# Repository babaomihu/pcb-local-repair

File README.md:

# PCB Local Repair

**KiCad 局部布线修复工具 / Local PCB Routing Repair for KiCad**

[中文](#中文) · [English](#english) · [安装与操作 / Installation](docs/INSTALL.md)

## 中文

PCB Local Repair 用于修复 KiCad PCB 中选定的未连接项。选择需要修复的连接后，工具自动确定局部范围、尝试布线，并检查连接关系、设计规则和修改范围，生成可审查、可另存的修复结果。

提供 **KiCad 插件和命令行** 两种使用方式，支持单条连接修复与多条连接批量处理。布线任务在工程副本上运行，结果通过验收后，由用户决定另存或采纳。

### 主要功能

- **待修连接发现**：列出支持修复的未连接项，支持焊盘、已有走线与过孔端点。
- **自动确定范围**：根据选定连接生成局部修复区域，无需手动填写坐标。
- **多连接处理**：一次选择多条连接，按队列处理，并支持修复顺序调整和候选组合。
- **局部修复策略**：支持补线、受控推挤、拆线重布、有限跨层打孔及已有过孔复用。
- **精细修改权限**：指定允许移动的走线、允许重填的铺铜和可使用的层；支持只调整跨区走线的区域内部分。
- **原生检查与保护**：重新填铜后检查目标连接、原有连接和完整板级 DRC，核对规则与受保护区域。
- **结果审查与保存**：提供修改清单、前后对比、失败诊断和运行日志；合格结果可一键另存，也可备份后明确采纳到原工程。

### 使用流程

1. 按[安装文档](docs/INSTALL.md)准备环境并安装插件或 CLI。
2. 打开已保存的 PCB 工程，检查待修连接。
3. 选择一条或多条连接，设置允许的修改，启动修复。
4. 查看结果与修改清单，将通过验收的结果另存，或明确采纳。

命令行示例：

```sh
# 检查待修连接
pcb-local inspect --config runtime.json --board /path/to/board.kicad_pcb \
  --auto-region --layer F.Cu --out-dir tasks/inspect-001

# 将 TARGET_ID 替换为检查结果中的连接 ID
pcb-local repair --config runtime.json --board /path/to/board.kicad_pcb \
  --auto-region --layer F.Cu --inspection tasks/inspect-001/result.json \
  --target TARGET_ID --signal-kind ordinary-single-ended \
  --candidate-strategy auto --out-dir tasks/repair-001

# 另存通过验收的修复结果
pcb-local export-result tasks/repair-001 --destination outputs/repaired-001
```

当前版本 **0.9.5.dev13**，适用环境为 **macOS Apple Silicon、Python 3.12、KiCad 10.0.4**。面向普通单端信号的局部修复；具体参数、批量操作和插件安装见[使用文档](docs/INSTALL.md)。

## English

PCB Local Repair repairs selected unfinished connections in KiCad PCB projects. After you select a connection, it determines a local region, attempts routing, and checks connectivity, design rules, and modification permissions to produce a result you can review and save.

Use it through a **KiCad plugin or command-line interface**. It supports individual connections and selected batches. Routing runs on project copies; accepted results can be exported or explicitly adopted by the user.

### Features

- **Connection discovery:** list eligible unfinished connections involving pads, existing tracks, and vias.
- **Automatic local regions:** derive the repair area from the selected connection without manually entering coordinates.
- **Batch repair:** select multiple connections, process a queue, and use ordering and candidate-combination strategies.
- **Local routing strategies:** add tracks, perform controlled shove and rip-up/reroute, add a bounded number of through vias, and reuse existing vias.
- **Explicit permissions:** select movable tracks, refillable zones, and permitted layers; modify only the in-region portion of eligible tracks crossing the boundary.
- **Native validation:** refill zones, check target and existing connectivity, run full-board DRC, and verify rules and protected regions.
- **Review and delivery:** inspect change lists, before/after reports, failure diagnostics, and logs. Export accepted results or explicitly adopt them with a backup.

### Workflow

1. Follow the [installation guide](docs/INSTALL.md) to prepare the runtime and install the plugin or CLI.
2. Inspect a saved PCB project for eligible unfinished connections.
3. Select one or more connections, choose modification permissions, and start repair.
4. Review the changes, then export or explicitly adopt accepted results.

The CLI example above demonstrates inspection, repair, and export. Replace `TARGET_ID` with an ID returned by inspection.

Current version: **0.9.5.dev13**. Target environment: **macOS Apple Silicon, Python 3.12, KiCad 10.0.4**. The tool handles local repairs of ordinary single-ended signals. See the [usage guide](docs/INSTALL.md) for batch processing, permissions, and plugin setup.

## 目录 / Repository layout

```text
src/pcb_local/     CLI、修复策略与验收 / CLI, repair strategies and validation
kicad_plugin/      KiCad 插件 / KiCad launcher
scripts/          安装与构建脚本 / Setup and build scripts
patches/          依赖补丁 / Dependency patches
tests/            代码回归测试 / Regression tests
examples/         自建机制示例 / Authored mechanism examples
docs/             安装与测试文档 / Installation and validation documentation
licenses/         许可文件 / License texts
```

## 许可证 / License

项目代码采用 [GPL-3.0-or-later](LICENSE)。各文件的许可例外与归属见 [THIRD_PARTY_NOTICES.md](THIRD_PARTY_NOTICES.md)。

Project code is licensed under [GPL-3.0-or-later](LICENSE). File-specific exceptions and attribution are documented in [THIRD_PARTY_NOTICES.md](THIRD_PARTY_NOTICES.md).

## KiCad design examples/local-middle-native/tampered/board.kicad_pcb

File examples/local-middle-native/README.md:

# Exact local-middle protection mechanism (CC0-1.0)

Authored synthetic geometry by this project. The input has one unfinished ordinary signal; the candidate connects it and manually replaces a long neighbouring track with exact original outside tails and an internal jog. This tests native acceptance and is **not an automatic routing success or a real-board success**. The tampered candidate moves one original outside-tail endpoint by 1 nm and must be rejected.

From the package root with the native runtime configured:

```bash
pcb-local verify --config runtime.json --board examples/local-middle-native/input/board.kicad_pcb --roi 4 9 26 18 --layer F.Cu --net REPAIR_SIGNAL --signal-kind ordinary-single-ended --local-track 602adc27-c63d-527d-9d39-4989a20f4f69 --candidate examples/local-middle-native/candidate/board.kicad_pcb --out-dir proof-accepted
pcb-local verify --config runtime.json --board examples/local-middle-native/input/board.kicad_pcb --roi 4 9 26 18 --layer F.Cu --net REPAIR_SIGNAL --signal-kind ordinary-single-ended --local-track 602adc27-c63d-527d-9d39-4989a20f4f69 --candidate examples/local-middle-native/tampered/board.kicad_pcb --out-dir proof-rejected
```

Expected: accepted (21 native/protection checks), then protection_violation. Use new output folders when repeating. No user project is overwritten. These fixture files are dedicated to the public domain under CC0-1.0: https://creativecommons.org/publicdomain/zero/1.0/.

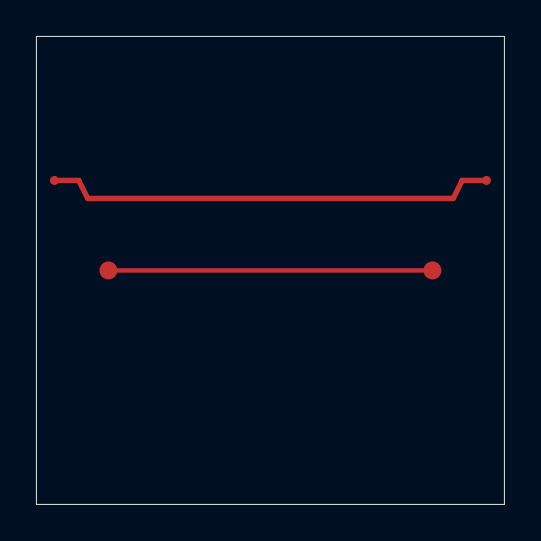
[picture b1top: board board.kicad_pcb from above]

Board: 2 copper layers, 26.0 x 26.0 mm, 4 parts (0 on the bottom side), 2 nets.

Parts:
A: Pad
LEFT: Anchor
RIGHT: Anchor
Z: Pad

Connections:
NEIGHBOUR: LEFT.1, RIGHT.1
REPAIR_SIGNAL: A.1, Z.1
